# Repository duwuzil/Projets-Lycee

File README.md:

#Projet en cours d'éléctronique (BTS CIEL ER 1er ANNEE) :
étudiants du lycée louis modeste leroy en 1ere année de BTS ciel ER ?
je suis passé par la, voici mes miniprojets qu'on a du rendre au cours de l'année.

pour comprendre

##MINIPROJ : le début de l'aventure du poulet :
--  a  ajouter.
-- terminer 

##MINPROJ 2 : l'épopée divine du poulet :
-- x
-- terminer

#Arborescence :
dans epopee du poulet tu trouvera un dossier Programmation et KiCad ainsi qu'un compte Rendu, sert toi du compte Rendu il m'a apporté une bonne note (des choses sont a revoir)
dans programmation tu aura la partie python qui tourne sur le pc
et arduino qui tourne sur l'atmega328
Dans Kicad tu trouvera les schema ainsi que les traces du pcb

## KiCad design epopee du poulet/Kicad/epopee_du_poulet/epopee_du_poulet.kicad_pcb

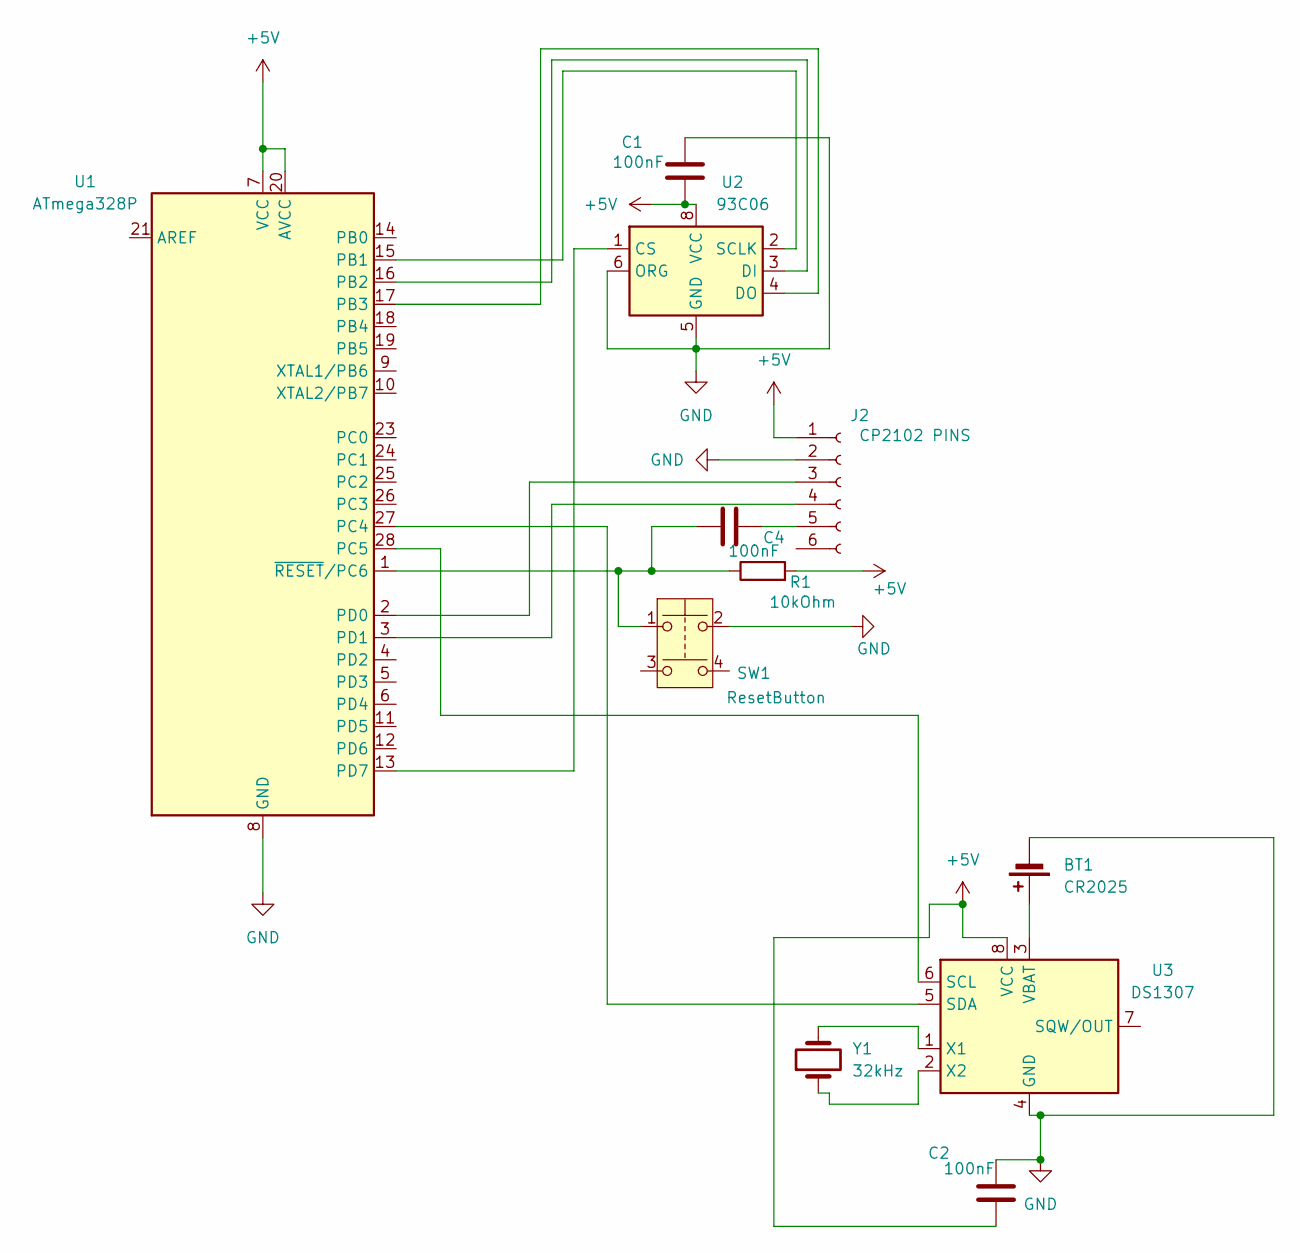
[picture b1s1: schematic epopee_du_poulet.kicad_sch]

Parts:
BT1: CR2025; Battery_Panasonic_CR2032-HFN_Horizontal_CircularHoles
C1, C2, C4: 100nF; C_0805_2012Metric_Pad1.18x1.45mm_HandSolder
J2: CP2102 PINS; PinSocket_1x06_P2.54mm_Vertical
R1: 10kOhm; R_Axial_DIN0204_L3.6mm_D1.6mm_P2.54mm_Vertical
SW1: ResetButton; SW_PUSH_6mm
U1: ATmega328P; DIP-28_W7.62mm
U2: 93C06; DIP-8_W7.62mm
U3: DS1307; DIP-8_W7.62mm
Y1: 32kHz; Crystal_Round_D3.0mm_Vertical

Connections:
+5V: C1.2, C2.2, J2.1, R1.2, U1.7 (VCC), U1.20 (AVCC), U2.8 (VCC), U3.8 (VCC)
GND: BT1.2 (-), C1.1, C2.1, J2.2, SW1.2, U1.8 (GND), U1.22 (GND), U2.5 (GND), U2.6 (ORG), U3.4 (GND)
unnamed: BT1.1 (+), U3.3 (VBAT)
unnamed: J2.3, U1.2 (PD0)
unnamed: J2.4, U1.3 (PD1)
unnamed: C4.2, J2.5
unnamed: U1.15 (PB1), U2.2 (SCLK)
unnamed: U1.16 (PB2), U2.3 (DI)
unnamed: U1.17 (PB3), U2.4 (DO)
unnamed: U1.27 (PC4), U3.5 (SDA)
unnamed: U1.28 (PC5), U3.6 (SCL)
unnamed: U1.13 (PD7), U2.1 (CS)
unnamed: C4.1, R1.1, SW1.1, U1.1 (~RESET/PC6)
unnamed: U3.1 (X1), Y1.2
unnamed: U3.2 (X2), Y1.1

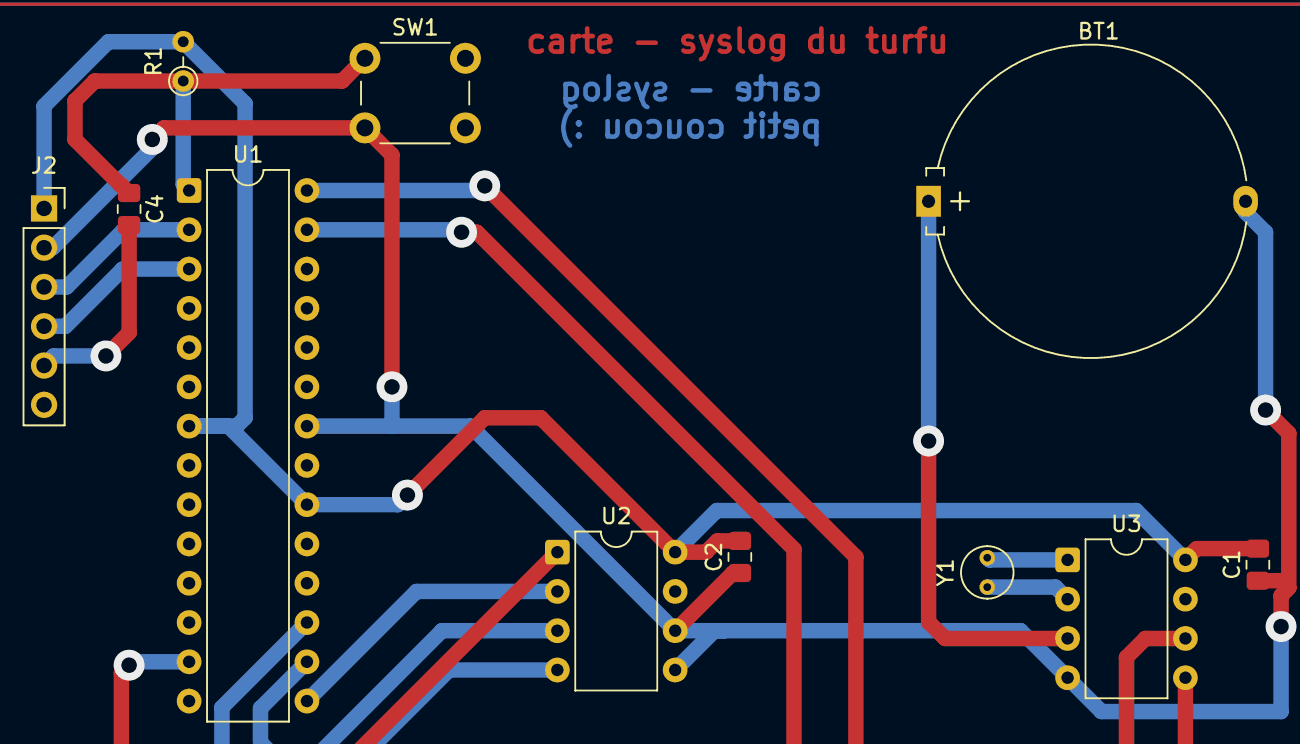
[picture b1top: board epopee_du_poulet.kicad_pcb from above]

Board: 2 copper layers, 11 parts (0 on the bottom side), 15 nets.

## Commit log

2025-02-24 Create a
2025-02-24 ajout de kicad
2025-02-24 change
2025-02-26 progs
2025-02-27 gros travail
2025-02-27 changement du code lecture de port serie
2025-02-27 pushing et forcing..
2025-03-01 completation du eeprom lien série et rtc
2025-03-03 coucou toi
2025-03-05 ajout du kicad
2025-03-06 derniere version du pcb
2025-03-20 ajout du programme en python
2025-03-20 FIN DU PROJET
